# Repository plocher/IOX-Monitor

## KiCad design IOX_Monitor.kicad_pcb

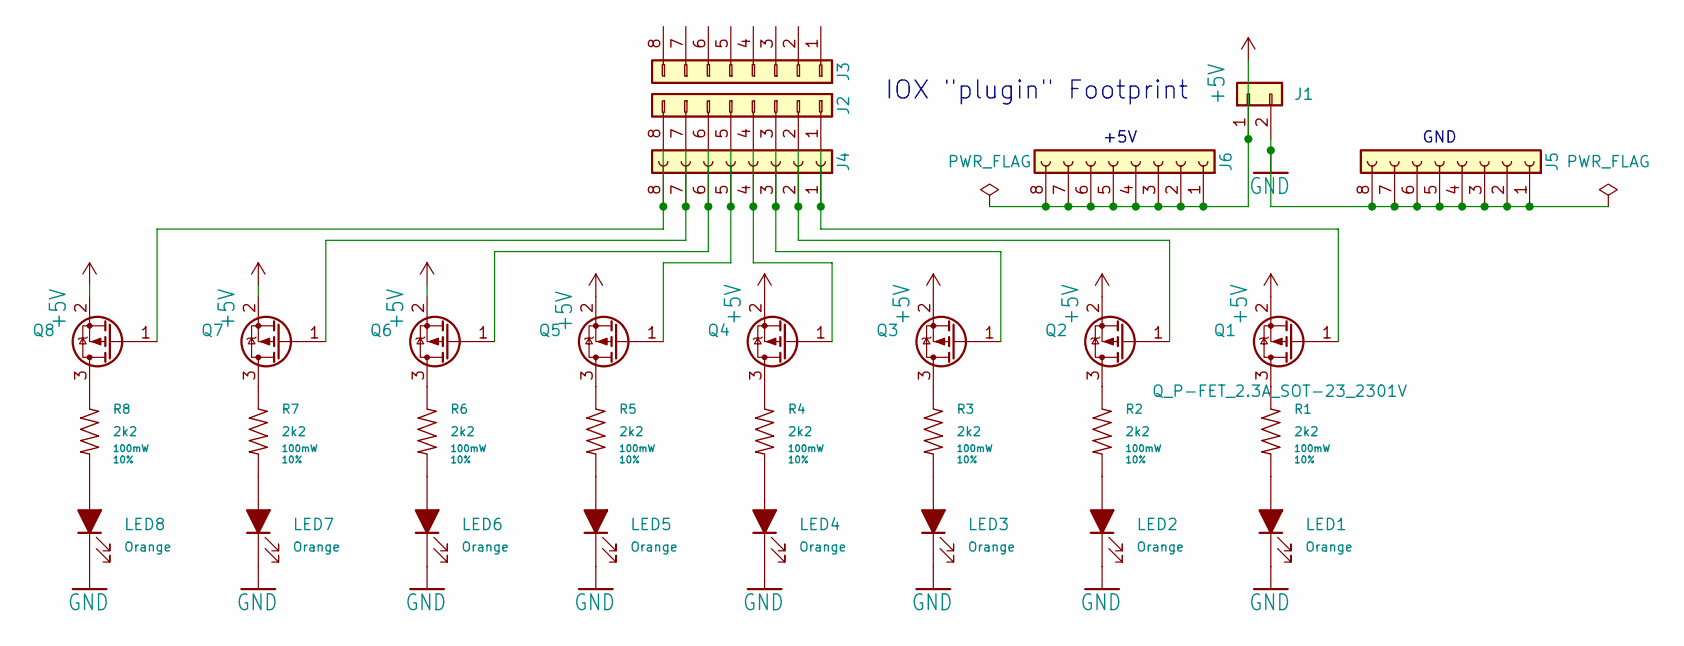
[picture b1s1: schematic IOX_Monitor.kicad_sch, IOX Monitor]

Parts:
J1: Conn_01x02; PinHeader_1x02_P2.54mm_Vertical
J2, J3: Conn_01x08; PinHeader_1x08_P2.54mm_Vertical
J4, J5, J6: Conn_01x08
LED1, LED2, LED3, LED4, LED5, LED6, LED7, LED8: Orange; 0603-LED
Q1, Q2, Q3, Q4, Q5, Q6, Q7, Q8: Q_P-FET_2.3A_SOT-23_2301V; SOT-23
R1, R2, R3, R4, R5, R6, R7, R8: 2k2; 0603-RES; Tolerance 10%

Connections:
+5V: J1.1, J6.1, J6.2, J6.3, J6.4, J6.5, J6.6, J6.7, J6.8, Q1.2 (S), Q2.2 (S), Q3.2 (S), Q4.2 (S), Q5.2 (S), Q6.2 (S), Q7.2 (S), Q8.2 (S)
GND: J1.2, J5.1, J5.2, J5.3, J5.4, J5.5, J5.6, J5.7, J5.8, LED1.1 (K), LED2.1 (K), LED3.1 (K), LED4.1 (K), LED5.1 (K), LED6.1 (K), LED7.1 (K), LED8.1 (K)
unnamed: J2.1, J4.1, Q1.1 (G)
unnamed: J2.2, J4.2, Q2.1 (G)
unnamed: J2.3, J4.3, Q3.1 (G)
unnamed: J2.4, J4.4, Q4.1 (G)
unnamed: J2.5, J4.5, Q5.1 (G)
unnamed: J2.6, J4.6, Q6.1 (G)
unnamed: J2.7, J4.7, Q7.1 (G)
unnamed: J2.8, J4.8, Q8.1 (G)
unnamed: LED1.2 (A), R1.2
unnamed: LED2.2 (A), R2.2
unnamed: LED3.2 (A), R3.2
unnamed: LED4.2 (A), R4.2
unnamed: LED5.2 (A), R5.2
unnamed: LED6.2 (A), R6.2
unnamed: LED7.2 (A), R7.2
unnamed: LED8.2 (A), R8.2
unnamed: Q1.3 (D), R1.1
unnamed: Q2.3 (D), R2.1
unnamed: Q3.3 (D), R3.1
unnamed: Q4.3 (D), R4.1
unnamed: Q5.3 (D), R5.1
unnamed: Q6.3 (D), R6.1
unnamed: Q7.3 (D), R7.1
unnamed: Q8.3 (D), R8.1

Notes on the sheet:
GND
IOX "plugin" Footprint
+5V

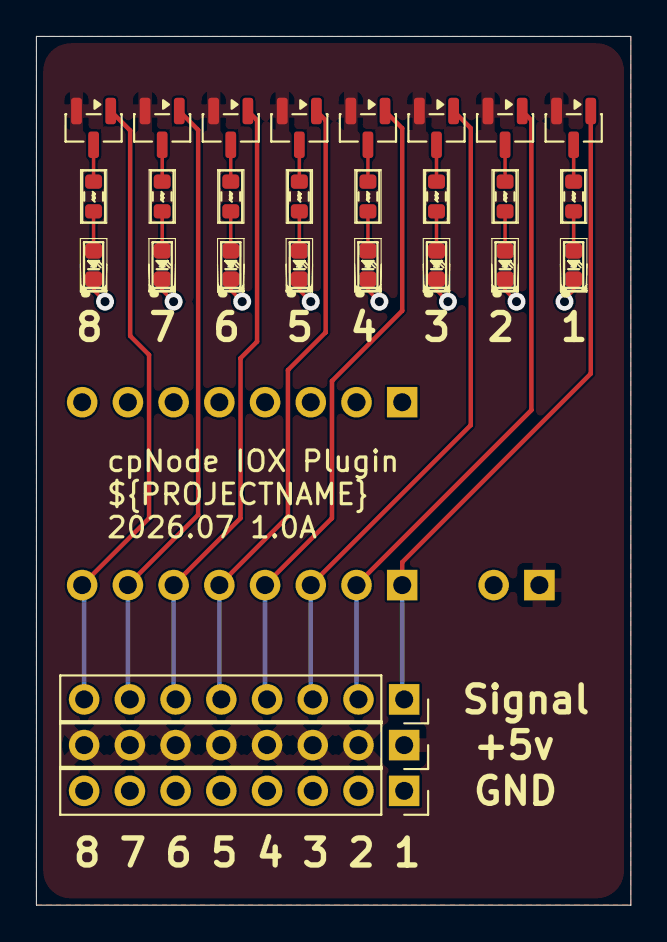
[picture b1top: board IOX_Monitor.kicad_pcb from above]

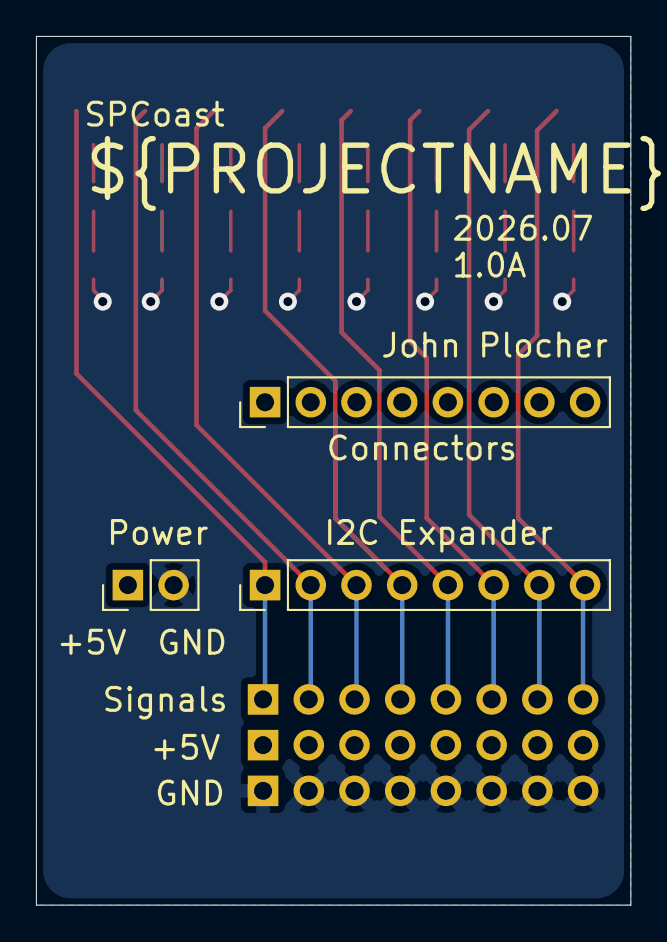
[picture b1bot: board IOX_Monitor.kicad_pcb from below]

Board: 2 copper layers, 33.0 x 48.3 mm, 30 parts (3 on the bottom side), 26 nets.
